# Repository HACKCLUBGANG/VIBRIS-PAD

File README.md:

# VIBRIS-PAD

My First Hardware project VIBRIS PAD! I followed the tutorial for everything but added my own stuff with some help of the slack community!

# Overview

This is my first time using Kicad. This used 12 MX Style Switches. I added some stuff that i wanted to because my granda is obsessed with god so i added name of god,godess.

# CAD ASSEMBLED
 NOTE - after the last review i added the 

# KiCad Schematic

A Key Matrix

Leds

# KiCad PCB

VERRY SORRY BECAUSE I DONT KNOW  HOW TO PLACE TRACKS NEATLY.

3D VIEW

# CASE FITTING

# BOM

Seeed XIAO RP2040 | 12x MX-Style switches 1u size | 12x Blank DSA keycaps (White) 1u size | 16x SK6812 MINI-E LEDs | Soldering kit | 1x 0.91 inch OLED displays | 12x Through-hole 1N4148 Diodes | PCB GRANT

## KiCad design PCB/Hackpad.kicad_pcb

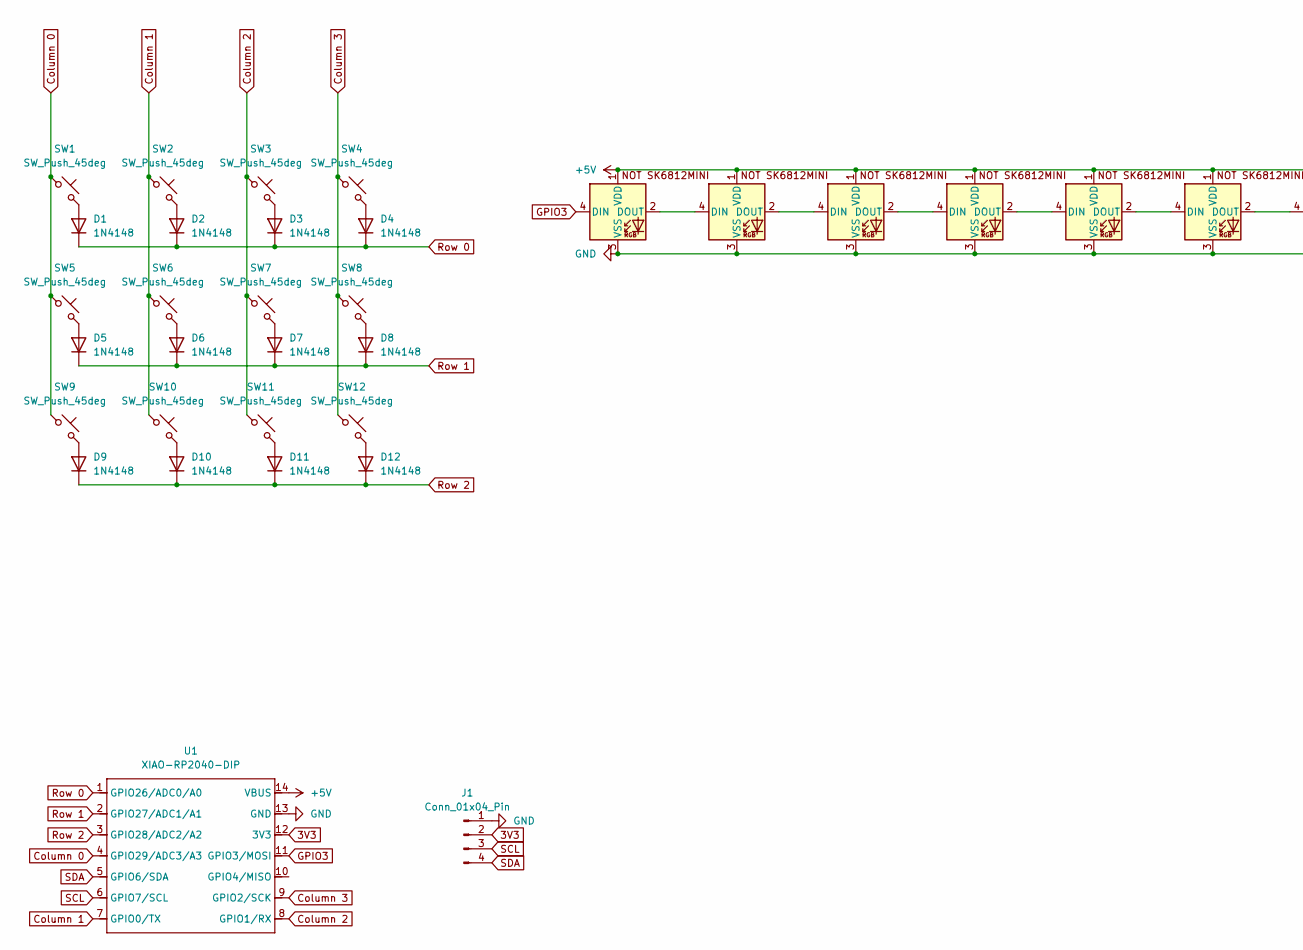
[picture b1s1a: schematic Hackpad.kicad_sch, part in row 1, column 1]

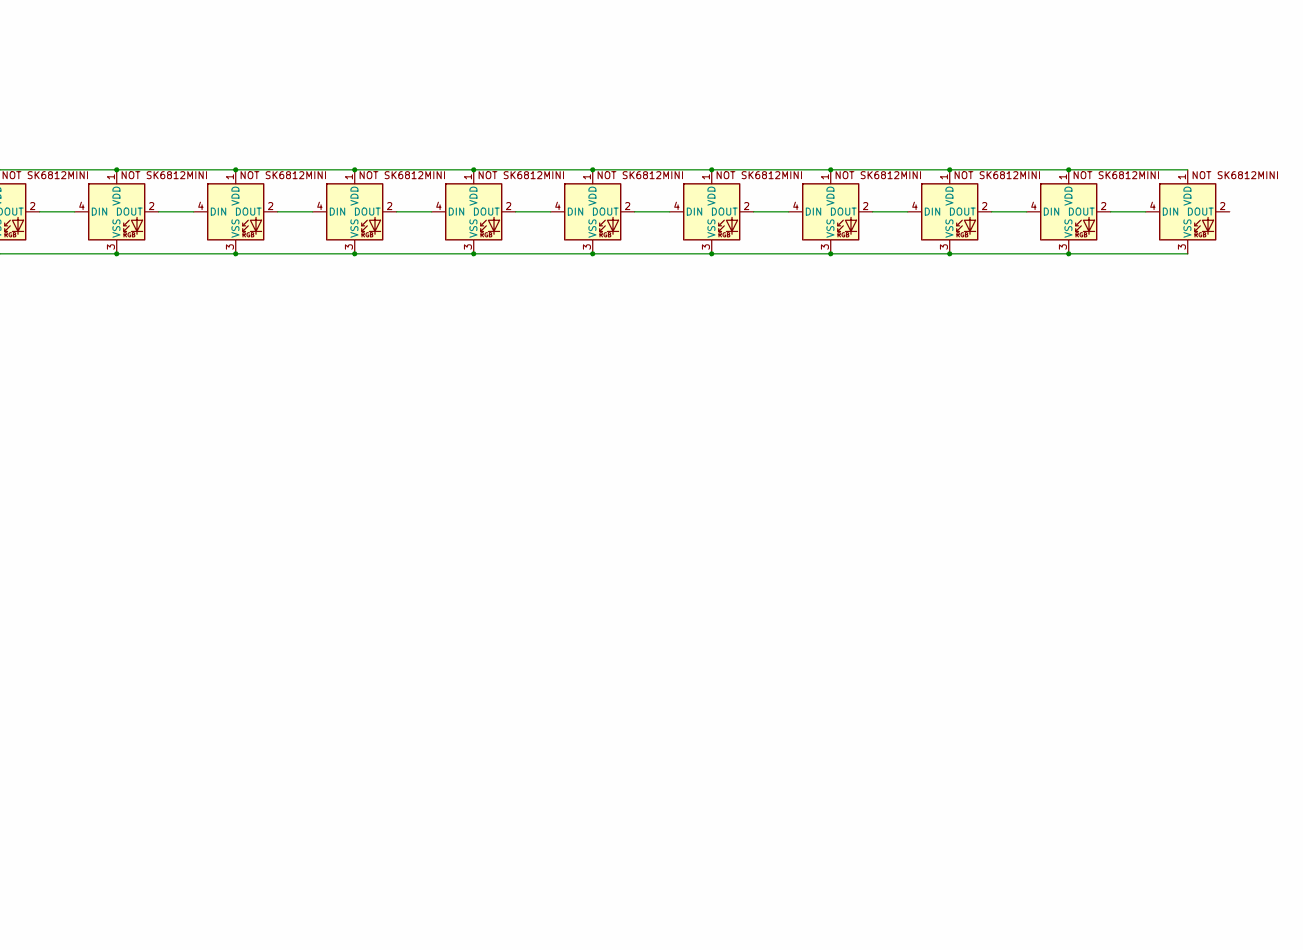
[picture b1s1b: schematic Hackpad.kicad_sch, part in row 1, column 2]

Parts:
D1, D2, D3, D4, D5, D6, D7, D8, D9, D10, D11, D12: 1N4148; D_DO-35_SOD27_P7.62mm_Horizontal
D33, D34, D35, D36, D37, D38, D39, D40, D41, D42, D43, D44, D45, D46, D47, D48: SK6812MINI-E; SK6812MINI-E_fixed
J1: Conn_01x04_Pin; SSD1306-0.91-OLED-4pin-128x32
SW1, SW2, SW3, SW4, SW5, SW6, SW7, SW8, SW9, SW10, SW11, SW12: SW_Push_45deg; SW_Cherry_MX_1.00u_PCB
U1: XIAO-RP2040-DIP

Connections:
3V3: J1.2, U1.12 (3V3)
+5V: D33.1 (VDD), D34.1 (VDD), D35.1 (VDD), D36.1 (VDD), D37.1 (VDD), D38.1 (VDD), D39.1 (VDD), D40.1 (VDD), D41.1 (VDD), D42.1 (VDD), D43.1 (VDD), D44.1 (VDD), D45.1 (VDD), D46.1 (VDD), D47.1 (VDD), D48.1 (VDD), U1.14 (VBUS)
Column 0: SW1.1, SW5.1, SW9.1, U1.4 (GPIO29/ADC3/A3)
Column 1: SW2.1, SW6.1, SW10.1, U1.7 (GPIO0/TX)
Column 2: SW3.1, SW7.1, SW11.1, U1.8 (GPIO1/RX)
Column 3: SW4.1, SW8.1, SW12.1, U1.9 (GPIO2/SCK)
GND: D33.3 (VSS), D34.3 (VSS), D35.3 (VSS), D36.3 (VSS), D37.3 (VSS), D38.3 (VSS), D39.3 (VSS), D40.3 (VSS), D41.3 (VSS), D42.3 (VSS), D43.3 (VSS), D44.3 (VSS), D45.3 (VSS), D46.3 (VSS), D47.3 (VSS), D48.3 (VSS), J1.1, U1.13 (GND)
GPIO3: D33.4 (DIN), U1.11 (GPIO3/MOSI)
unnamed: D1.2 (A), SW1.2
unnamed: D2.2 (A), SW2.2
unnamed: D3.2 (A), SW3.2
unnamed: D4.2 (A), SW4.2
unnamed: D5.2 (A), SW5.2
unnamed: D6.2 (A), SW6.2
unnamed: D7.2 (A), SW7.2
unnamed: D8.2 (A), SW8.2
unnamed: D9.2 (A), SW9.2
unnamed: D10.2 (A), SW10.2
unnamed: D11.2 (A), SW11.2
unnamed: D12.2 (A), SW12.2
unnamed: D33.2 (DOUT), D34.4 (DIN)
unnamed: D34.2 (DOUT), D35.4 (DIN)
unnamed: D35.2 (DOUT), D36.4 (DIN)
unnamed: D36.2 (DOUT), D37.4 (DIN)
unnamed: D37.2 (DOUT), D38.4 (DIN)
unnamed: D38.2 (DOUT), D39.4 (DIN)
unnamed: D39.2 (DOUT), D40.4 (DIN)
unnamed: D40.2 (DOUT), D41.4 (DIN)
unnamed: D41.2 (DOUT), D42.4 (DIN)
unnamed: D42.2 (DOUT), D43.4 (DIN)
unnamed: D43.2 (DOUT), D44.4 (DIN)
unnamed: D44.2 (DOUT), D45.4 (DIN)
unnamed: D45.2 (DOUT), D46.4 (DIN)
unnamed: D46.2 (DOUT), D47.4 (DIN)
unnamed: D47.2 (DOUT), D48.4 (DIN)
Row 0: D1.1 (K), D2.1 (K), D3.1 (K), D4.1 (K), U1.1 (GPIO26/ADC0/A0)
Row 1: D5.1 (K), D6.1 (K), D7.1 (K), D8.1 (K), U1.2 (GPIO27/ADC1/A1)
Row 2: D9.1 (K), D10.1 (K), D11.1 (K), D12.1 (K), U1.3 (GPIO28/ADC2/A2)
SCL: J1.3, U1.6 (GPIO7/SCL)
SDA: J1.4, U1.5 (GPIO6/SDA)

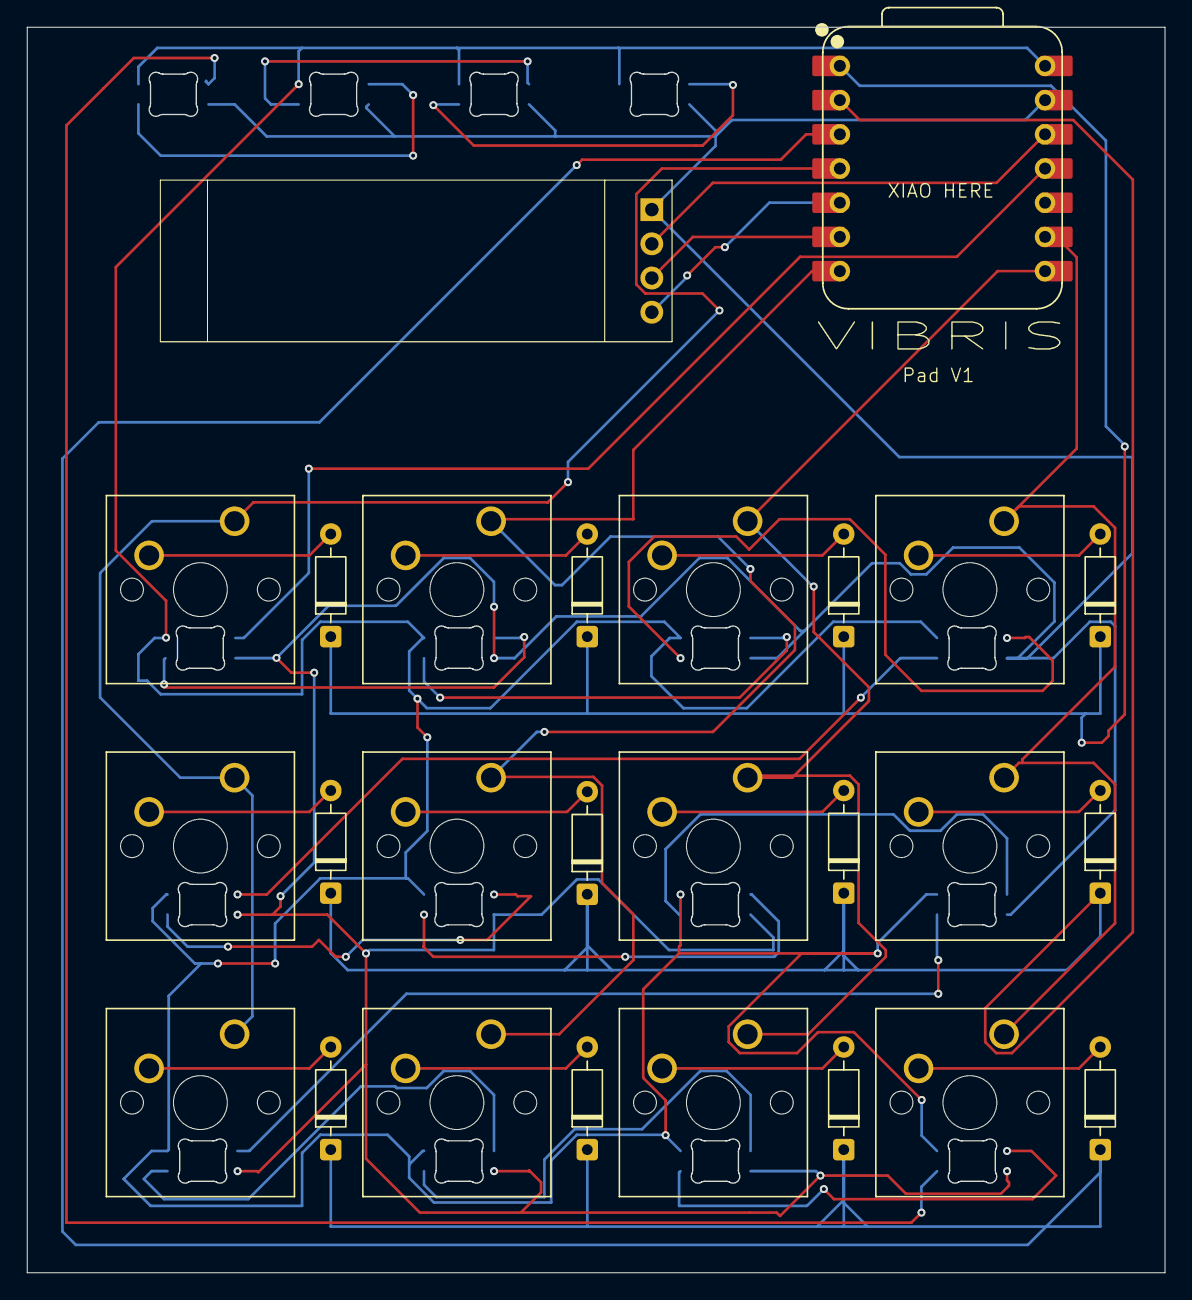
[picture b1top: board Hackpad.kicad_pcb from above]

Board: 2 copper layers, 84.5 x 92.5 mm, 42 parts (0 on the bottom side), 40 nets.

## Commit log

2026-01-03 Rename VIBRISPADASSEMBLED.step to CAD/VIBRISPADASSEMBLED.step
2026-01-03 Rename VIBRISASSEMBLEDCADFILE.step to CAD/VIBRISASSEMBLEDCADFILE.step
